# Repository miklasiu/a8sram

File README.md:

Atari 8bit Freddy and DRAM chips replacement.
---------------------------------------------

I created it because I had 32k SRAM chips available and needed to test if my Freddy was working (it was).
The board is intended for home manufacturing. There is only 1 via. I was able to do it using 3d printer with drill attachment and laser printer thermo-transfer. Make sure to solder on both sides where necessary or tell me how to make vias/holes conductive at home.

There are more reasonable Freddy and SRAM replacements avialble:

Pre-built:
- https://retrolemon.co.uk/atari-8bit-upgrades/81-freddie-module.html
- https://lotharek.pl/productdetail.php?id=233
- https://retrolemon.co.uk/atari-8bit-upgrades/114-sram-64kb.html
- https://lotharek.pl/productdetail.php?id=291

Schematics:
- https://github.com/prcoder-1/a8-sram64kb
  
What's left from Freddy is then just frequency /4 divider you can do on 7474.

Finished thing:

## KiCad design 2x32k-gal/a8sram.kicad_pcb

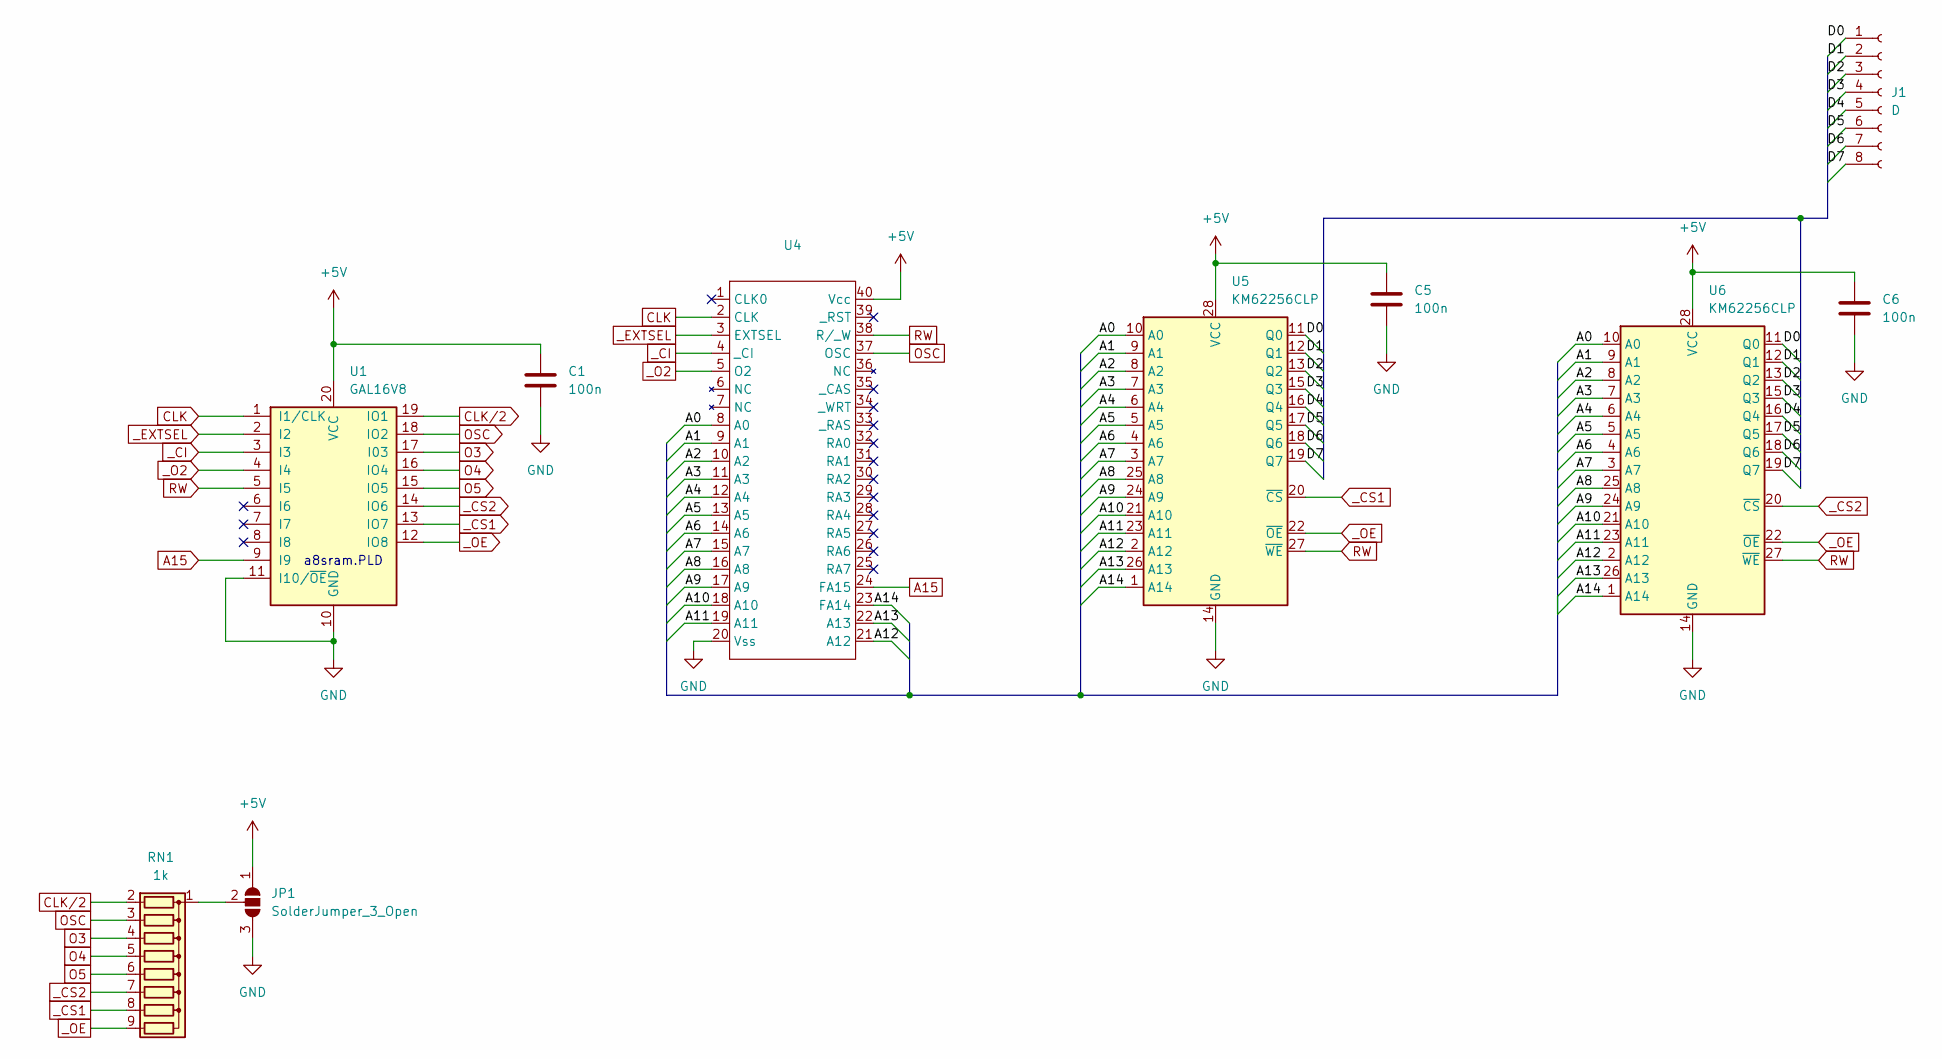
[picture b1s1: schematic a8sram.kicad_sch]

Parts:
C1, C5, C6: 100n; C_0805_2012Metric_Pad1.18x1.45mm_HandSolder
J1: D; PinHeader_1x08_P2.54mm_Vertical
JP1: SolderJumper_3_Open; SolderJumper-3_P1.3mm_Open_RoundedPad1.0x1.5mm
RN1: 1k; R_Array_SIP9
U1: GAL16V8; DIP-20_W7.62mm
U4: DIP-40_W15.24mm
U5, U6: KM62256CLP; DIP-28_W7.62mm

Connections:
+5V: C1.1, C5.1, C6.1, JP1.1 (A), U1.20 (VCC), U4.40 (Vcc), U5.28 (VCC), U6.28 (VCC)
/A0: U4.8 (A0), U5.10 (A0), U6.10 (A0)
/A1: U4.9 (A1), U5.9 (A1), U6.9 (A1)
/A2: U4.10 (A2), U5.8 (A2), U6.8 (A2)
/A3: U4.11 (A3), U5.7 (A3), U6.7 (A3)
/A4: U4.12 (A4), U5.6 (A4), U6.6 (A4)
/A5: U4.13 (A5), U5.5 (A5), U6.5 (A5)
/A6: U4.14 (A6), U5.4 (A6), U6.4 (A6)
/A7: U4.15 (A7), U5.3 (A7), U6.3 (A7)
/A8: U4.16 (A8), U5.25 (A8), U6.25 (A8)
/A9: U4.17 (A9), U5.24 (A9), U6.24 (A9)
/A10: U4.18 (A10), U5.21 (A10), U6.21 (A10)
/A11: U4.19 (A11), U5.23 (A11), U6.23 (A11)
/A12: U4.21 (A12), U5.2 (A12), U6.2 (A12)
/A13: U4.22 (A13), U5.26 (A13), U6.26 (A13)
/A14: U4.23 (FA14), U5.1 (A14), U6.1 (A14)
/D0: J1.1, U5.11 (Q0), U6.11 (Q0)
/D1: J1.2, U5.12 (Q1), U6.12 (Q1)
/D2: J1.3, U5.13 (Q2), U6.13 (Q2)
/D3: J1.4, U5.15 (Q3), U6.15 (Q3)
/D4: J1.5, U5.16 (Q4), U6.16 (Q4)
/D5: J1.6, U5.17 (Q5), U6.17 (Q5)
/D6: J1.7, U5.18 (Q6), U6.18 (Q6)
/D7: J1.8, U5.19 (Q7), U6.19 (Q7)
A15: U1.9 (I9), U4.24 (FA15)
CLK: U1.1 (I1/CLK), U4.2 (CLK)
CLK/2: RN1.2 (R1), U1.19 (IO1)
GND: C1.2, C5.2, C6.2, JP1.3 (B), U1.10 (GND), U1.11 (I10/~OE), U4.20 (Vss), U5.14 (GND), U6.14 (GND)
unnamed: JP1.2 (C), RN1.1 (common)
O3: RN1.4 (R3), U1.17 (I03)
O4: RN1.5 (R4), U1.16 (IO4)
O5: RN1.6 (R5), U1.15 (IO5)
OSC: RN1.3 (R2), U1.18 (IO2), U4.37 (OSC)
RW: U1.5 (I5), U4.38 (R/_W), U5.27 (~WE), U6.27 (~WE)
_CI: U1.3 (I3), U4.4 (_CI)
_CS1: RN1.8 (R7), U1.13 (IO7), U5.20 (~CS)
_CS2: RN1.7 (R6), U1.14 (IO6), U6.20 (~CS)
_EXTSEL: U1.2 (I2), U4.3 (EXTSEL)
_O2: U1.4 (I4), U4.5 (O2)
_OE: RN1.9 (R8), U1.12 (IO8), U5.22 (~OE), U6.22 (~OE)

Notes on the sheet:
a8sram.PLD

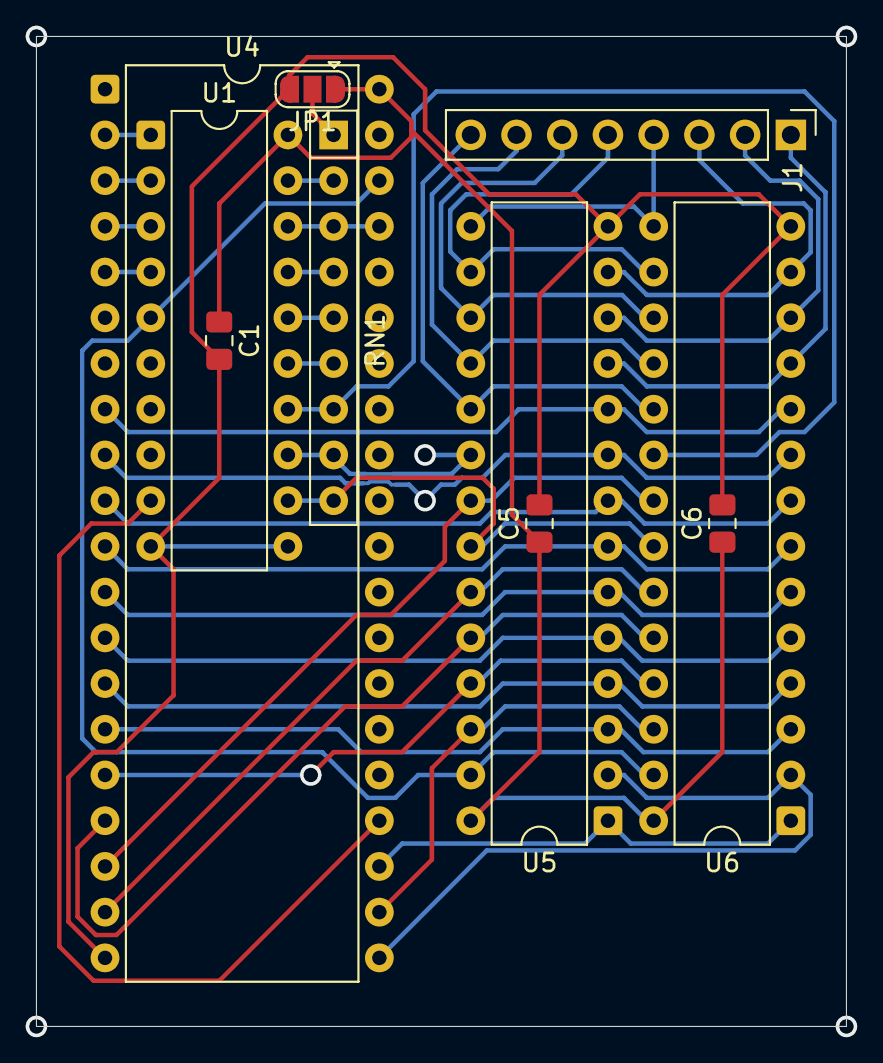
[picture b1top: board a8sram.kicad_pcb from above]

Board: 2 copper layers, 45.0 x 55.0 mm, 10 parts (0 on the bottom side), 40 nets.

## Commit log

2025-10-10 rm lock files
2025-10-21 2x32k-gal works!
2025-10-26 Cleanup.
2025-10-26 Cleanup 2
2025-10-26 Update README formatting.
    Corrected formatting and added links for clarity.
2025-10-26 Enhance README with manufacturing and soldering info
2025-10-26 Photos
2025-10-26 Update README with finished project images
2025-10-26 Some comments in GAL code
